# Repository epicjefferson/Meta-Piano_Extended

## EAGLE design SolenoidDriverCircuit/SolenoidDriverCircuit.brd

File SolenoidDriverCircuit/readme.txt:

Este circuito fue diseñado por Guillermo Ramirez (gramirez.rivera[at]gmail[dot]com)
para el proyecto del Meta-Piano Extendido de Epic Jefferson y Themis Cádiz.

Fue diseńado en el programa Eagle.

____________________________________________________________________________________

This circuit was designed by Guillermo Ramirez
for Epic Jefferson and Themis Cádiz´s Meta-Piano Extended project.

It was designed in Eagle software.

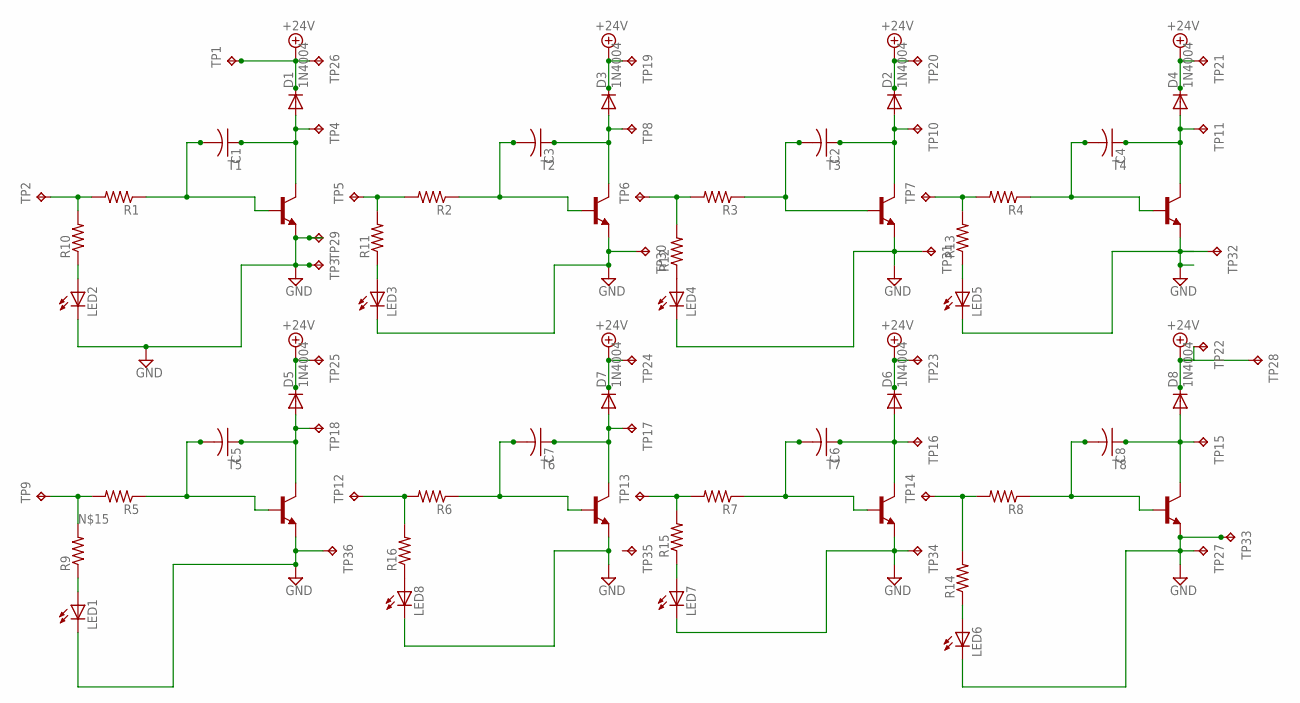
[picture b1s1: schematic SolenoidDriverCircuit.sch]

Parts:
C1, C2, C3, C4, C5, C6, C7, C8: C-US050-024X044; C050-024X044
D1, D2, D3, D4, D5, D6, D7, D8: 1N4004; DO41-10
LED1, LED2, LED3, LED4, LED5, LED6, LED7, LED8: LED_ELD260; LED_LD260
R1, R2, R3, R4, R5, R6, R7, R8, R9, R10, R11, R12, R13, R14, R15, R16: R-US_0207/2V; 0207/2V
T1, T2, T3, T4, T5, T6, T7, T8: -NPN-TO220V; TO220V
TP1, TP3, TP4, TP8, TP10, TP11, TP15, TP16, TP17, TP18, TP19, TP20, TP21, TP22, TP23, TP24, TP25, TP26, TP27, TP28: TPPAD1-13Y; P1-13Y
TP2, TP5, TP6, TP7, TP9, TP12, TP13, TP14, TP29, TP30, TP31, TP32, TP33, TP34, TP35, TP36: TPPAD1-13; P1-13

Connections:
+24V: D1.C, D2.C, D3.C, D4.C, D5.C, D6.C, D7.C, D8.C, TP1.TP, TP19.TP, TP20.TP, TP21.TP, TP22.TP, TP23.TP, TP24.TP, TP25.TP, TP26.TP, TP28.TP
GND: LED1.K (C), LED2.K (C), LED3.K (C), LED4.K (C), LED5.K (C), LED6.K (C), LED7.K (C), LED8.K (C), T1.3 (E), T2.3 (E), T3.3 (E), T4.3 (E), T5.3 (E), T6.3 (E), T7.3 (E), T8.3 (E), TP3.TP, TP27.TP, TP29.TP, TP30.TP, TP31.TP, TP32.TP, TP33.TP, TP34.TP, TP36.TP
unnamed: C1.1, D1.A, T1.2 (C), TP4.TP
unnamed: C1.2, R1.1, T1.1 (B)
unnamed: R1.2, R10.2, TP2.TP
unnamed: C2.1, D2.A, T3.2 (C), TP10.TP
unnamed: R3.2, R12.2, TP6.TP
unnamed: C3.1, D3.A, T2.2 (C), TP8.TP
unnamed: C3.2, R2.1, T2.1 (B)
unnamed: R2.2, R11.2, TP5.TP
unnamed: C4.1, D4.A, T4.2 (C), TP11.TP
unnamed: C4.2, R4.1, T4.1 (B)
unnamed: R4.2, R13.2, TP7.TP
unnamed: C5.1, D5.A, T5.2 (C), TP18.TP
unnamed: C5.2, R5.1, T5.1 (B)
unnamed: R5.2, R9.2, TP9.TP
unnamed: C6.1, D6.A, T7.2 (C), TP16.TP
unnamed: C6.2, R7.1, T7.1 (B)
unnamed: R7.2, R15.2, TP13.TP
unnamed: C7.1, D7.A, T6.2 (C), TP17.TP
unnamed: C7.2, R6.1, T6.1 (B)
unnamed: R6.2, R16.2, TP12.TP
unnamed: C8.1, D8.A, T8.2 (C), TP15.TP
unnamed: C8.2, R8.1, T8.1 (B)
unnamed: R8.2, R14.2, TP14.TP
unnamed: LED1.A, R9.1
unnamed: LED2.A, R10.1
unnamed: C2.2, R3.1, T3.1 (B)
unnamed: LED3.A, R11.1
unnamed: LED4.A, R12.1
unnamed: LED5.A, R13.1
unnamed: LED6.A, R14.1
unnamed: LED7.A, R15.1
unnamed: LED8.A, R16.1

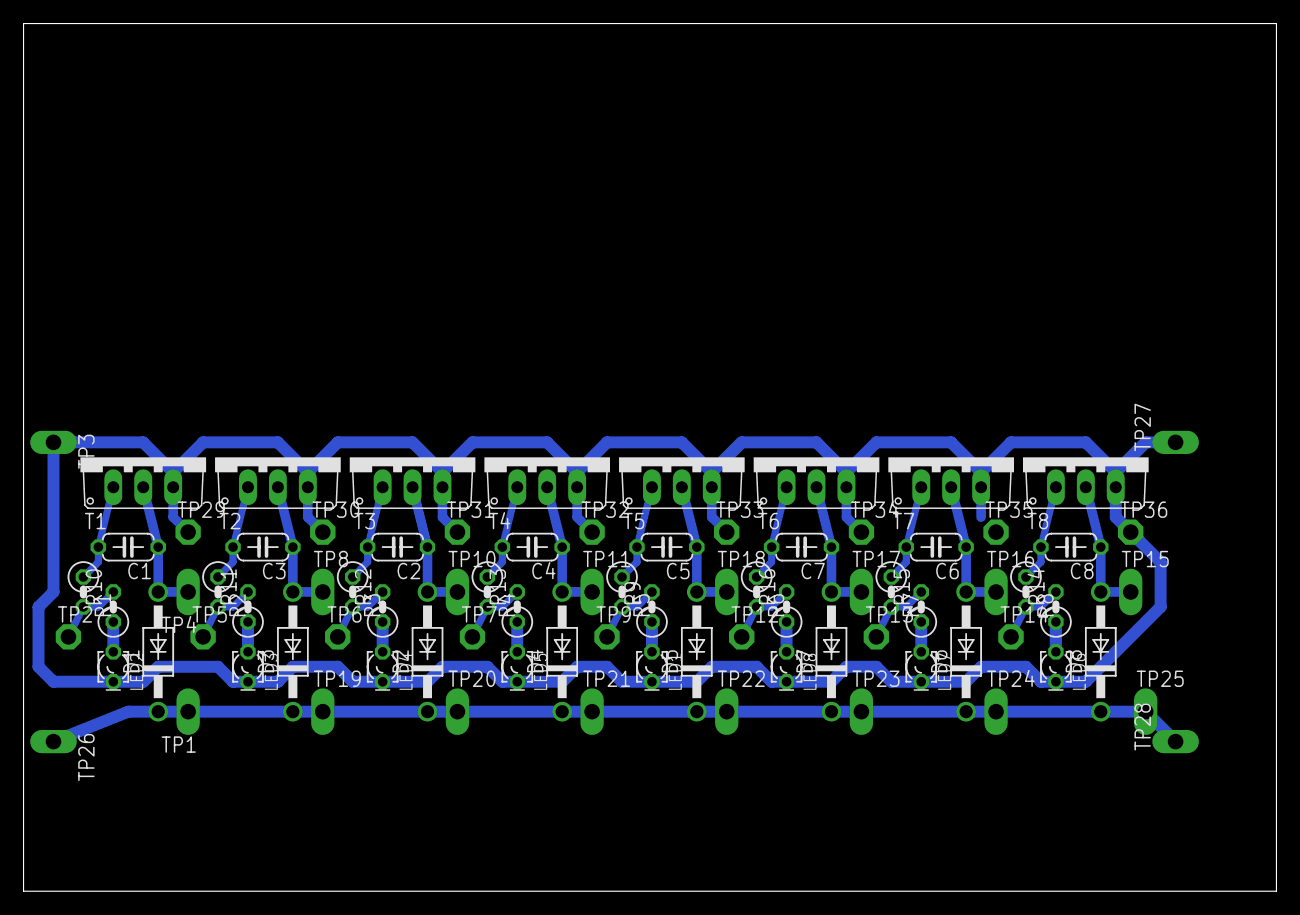
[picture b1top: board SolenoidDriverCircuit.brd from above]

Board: 2 copper layers, 106.3 x 73.7 mm, 84 parts (0 on the bottom side), 34 nets.

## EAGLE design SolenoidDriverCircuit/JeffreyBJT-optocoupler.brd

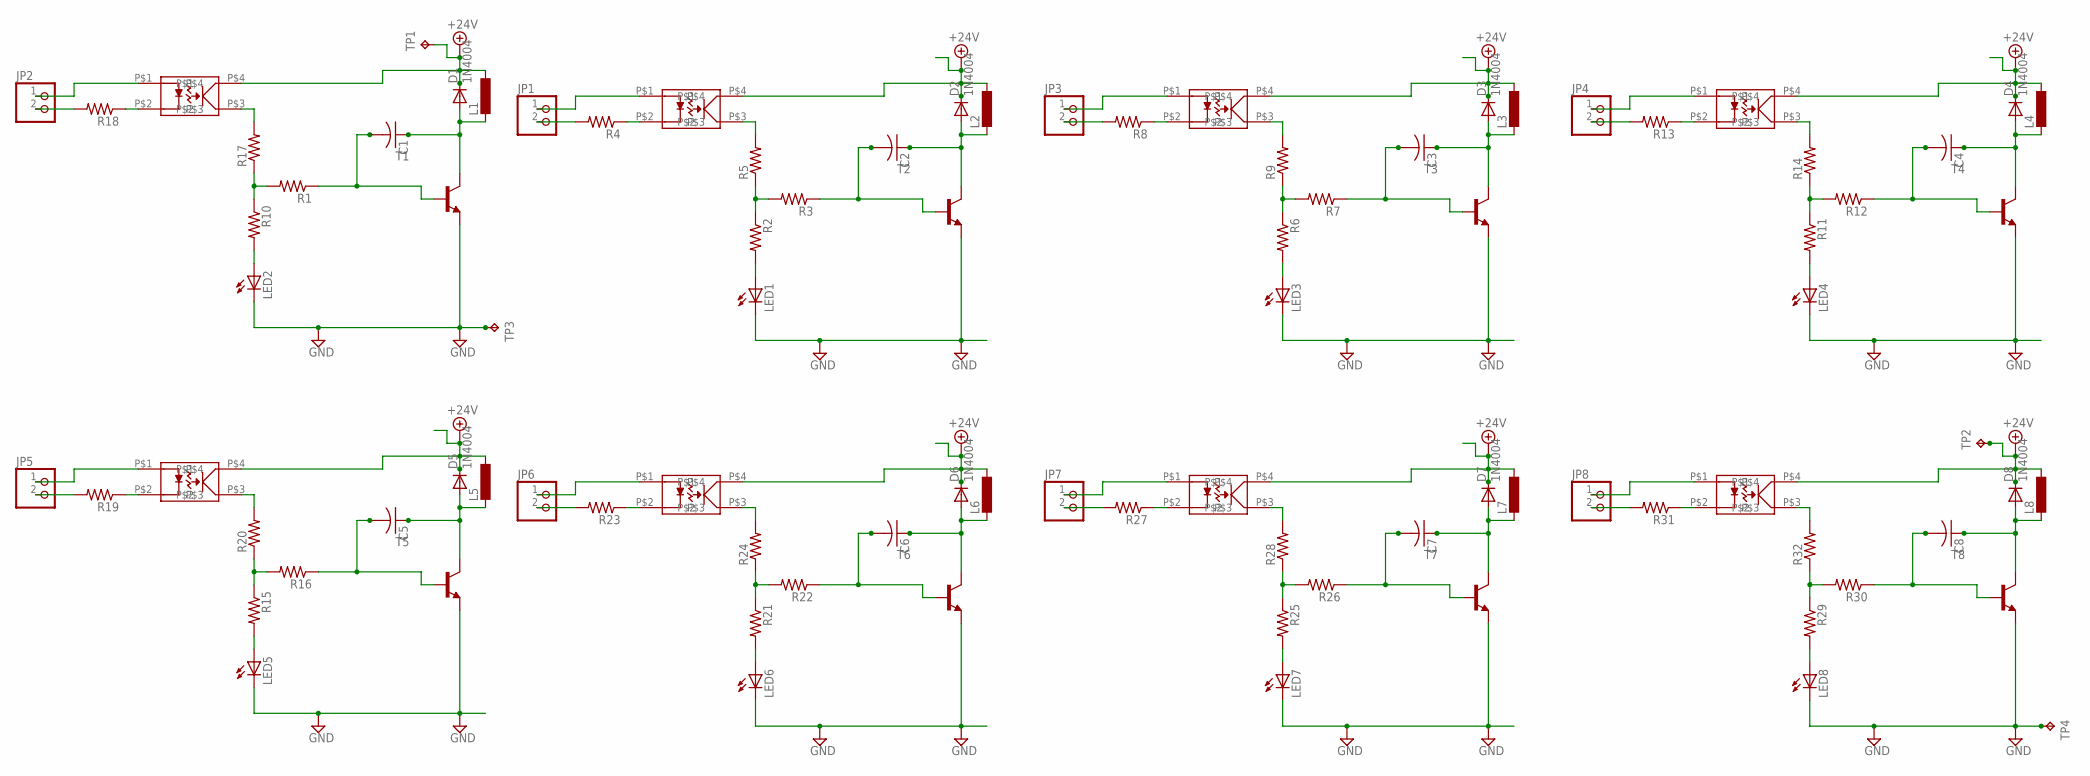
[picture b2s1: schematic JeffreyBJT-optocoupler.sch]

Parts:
C1, C2, C3, C4, C5, C6, C7, C8: C-US050-024X044; C050-024X044
D1, D2, D3, D4, D5, D6, D7, D8: 1N4004; DO41-10
JP1, JP2, JP3, JP4, JP5, JP6, JP7, JP8: PINHD-1X2; 1X02
L1, L2, L3, L4, L5, L6, L7, L8: L-EU0207/10; 0207/10
LED1, LED2, LED3, LED4, LED5, LED6, LED7, LED8: LED_ELD260; LED_LD260
R1, R2, R3, R4, R6, R7, R8, R10, R11, R12, R13, R15, R16, R18, R19, R21, R22, R23, R25, R26, R27, R29, R30, R31: R-US_0207/2V; 0207/2V
R5, R9, R14, R17, R20, R24, R28, R32: R-US_0207/7; 0207/7
T1, T2, T3, T4, T5, T6, T7, T8: -NPN-TO220V; TO220V
TP1, TP2, TP3, TP4: TPPAD1-13Y; P1-13Y
U$1, U$2, U$3, U$4, U$5, U$6, U$7, U$8: PS2501_TRU

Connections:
+24V: D1.C, D2.C, D3.C, D4.C, D5.C, D6.C, D7.C, D8.C, L1.1, L2.1, L3.1, L4.1, L5.1, L6.1, L7.1, L8.1, TP1.TP, TP2.TP, U$1.P$4, U$2.P$4, U$3.P$4, U$4.P$4, U$5.P$4, U$6.P$4, U$7.P$4, U$8.P$4
GND: LED1.K (C), LED2.K (C), LED3.K (C), LED4.K (C), LED5.K (C), LED6.K (C), LED7.K (C), LED8.K (C), T1.3 (E), T2.3 (E), T3.3 (E), T4.3 (E), T5.3 (E), T6.3 (E), T7.3 (E), T8.3 (E), TP3.TP, TP4.TP
unnamed: C1.1, D1.A, L1.2, T1.2 (C)
unnamed: C1.2, R1.1, T1.1 (B)
unnamed: R1.2, R10.1, R17.1
unnamed: C2.1, D2.A, L2.2, T2.2 (C)
unnamed: C2.2, R3.1, T2.1 (B)
unnamed: R2.1, R3.2, R5.1
unnamed: R5.2, U$2.P$3
unnamed: R4.1, U$2.P$2
unnamed: JP1.2, R4.2
unnamed: JP1.1, U$2.P$1
unnamed: LED1.A, R2.2
unnamed: C3.1, D3.A, L3.2, T3.2 (C)
unnamed: C3.2, R7.1, T3.1 (B)
unnamed: R6.1, R7.2, R9.1
unnamed: R9.2, U$3.P$3
unnamed: R8.1, U$3.P$2
unnamed: JP3.2, R8.2
unnamed: JP3.1, U$3.P$1
unnamed: LED3.A, R6.2
unnamed: C4.1, D4.A, L4.2, T4.2 (C)
unnamed: C4.2, R12.1, T4.1 (B)
unnamed: R11.1, R12.2, R14.1
unnamed: LED2.A, R10.2
unnamed: R14.2, U$4.P$3
unnamed: R13.1, U$4.P$2
unnamed: R17.2, U$1.P$3
unnamed: JP2.2, R18.2
unnamed: JP4.2, R13.2
unnamed: JP2.1, U$1.P$1
unnamed: JP4.1, U$4.P$1
unnamed: R18.1, U$1.P$2
unnamed: LED4.A, R11.2
unnamed: C5.1, D5.A, L5.2, T5.2 (C)
unnamed: C5.2, R16.1, T5.1 (B)
unnamed: R15.1, R16.2, R20.1
unnamed: R20.2, U$5.P$3
unnamed: R19.1, U$5.P$2
unnamed: JP5.2, R19.2
unnamed: JP5.1, U$5.P$1
unnamed: LED5.A, R15.2
unnamed: C6.1, D6.A, L6.2, T6.2 (C)
unnamed: C6.2, R22.1, T6.1 (B)
unnamed: R21.1, R22.2, R24.1
unnamed: R24.2, U$6.P$3
unnamed: R23.1, U$6.P$2
unnamed: JP6.2, R23.2
unnamed: JP6.1, U$6.P$1
unnamed: LED6.A, R21.2
unnamed: C7.1, D7.A, L7.2, T7.2 (C)
unnamed: C7.2, R26.1, T7.1 (B)
unnamed: R25.1, R26.2, R28.1
unnamed: R28.2, U$7.P$3
unnamed: R27.1, U$7.P$2
unnamed: JP7.2, R27.2
unnamed: JP7.1, U$7.P$1
unnamed: LED7.A, R25.2
unnamed: C8.1, D8.A, L8.2, T8.2 (C)
unnamed: C8.2, R30.1, T8.1 (B)
unnamed: R29.1, R30.2, R32.1
unnamed: R32.2, U$8.P$3
unnamed: R31.1, U$8.P$2
unnamed: JP8.2, R31.2
unnamed: JP8.1, U$8.P$1
unnamed: LED8.A, R29.2

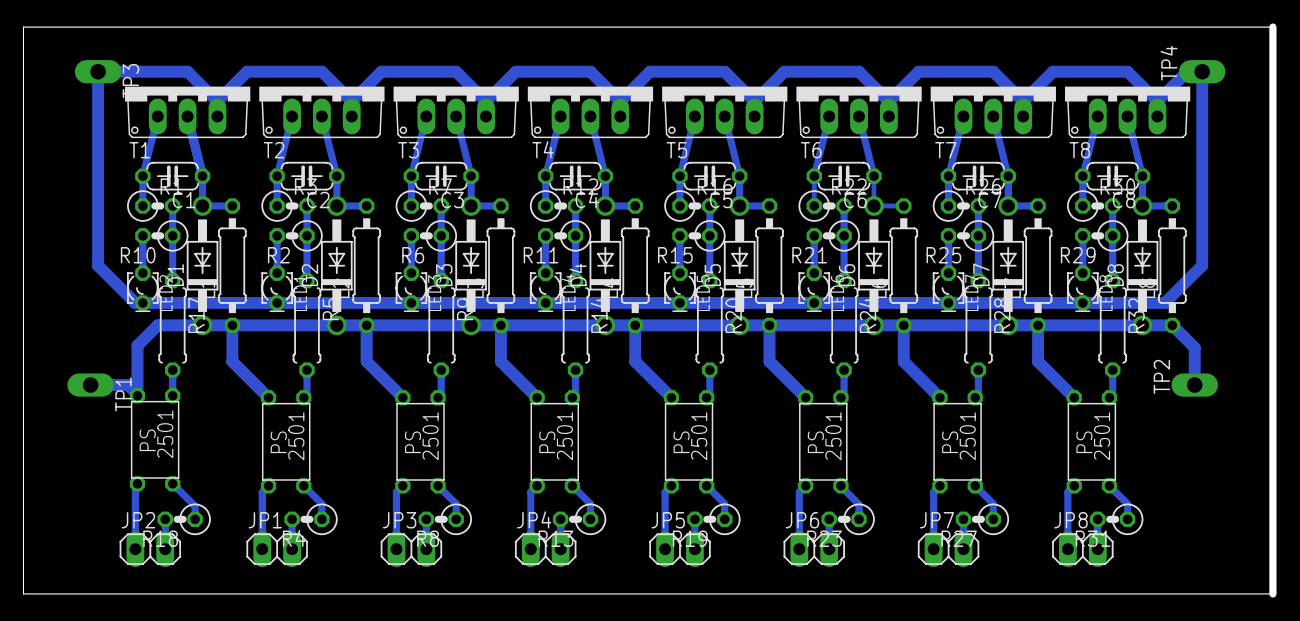
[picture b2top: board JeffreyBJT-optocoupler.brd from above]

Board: 2 copper layers, 106.0 x 48.2 mm, 92 parts (0 on the bottom side), 66 nets.

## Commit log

2013-11-14 uploading Solenoid Driver Schematics
2013-11-14 created meta-piano repo
2013-11-14 adding solenoiduino firmware
